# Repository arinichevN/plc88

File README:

Проект модульного контроллера plc88.
Инструментарий.
Электрические схемы и печатные платы разработаны с помощью KiCad. Библиотеки пользовательских компонентов для KiCad расположены в папке lib. Симуляция работы некоторых узлов производилась в программе https://falstad.com/circuit/circuitjs.html. Программное обеспечение для тестирования отдельных узлов написано на языке Си для Arduino IDE.
Предупреждение.
Представленные в этом проекте аппаратные и программные средства явлются прототипами и не оптимизированы для производства и профессионального использования. Они подходят для обучения но при использовании в реальных ситуациях, нет никакой гарантии, что они будут работать без аварий.

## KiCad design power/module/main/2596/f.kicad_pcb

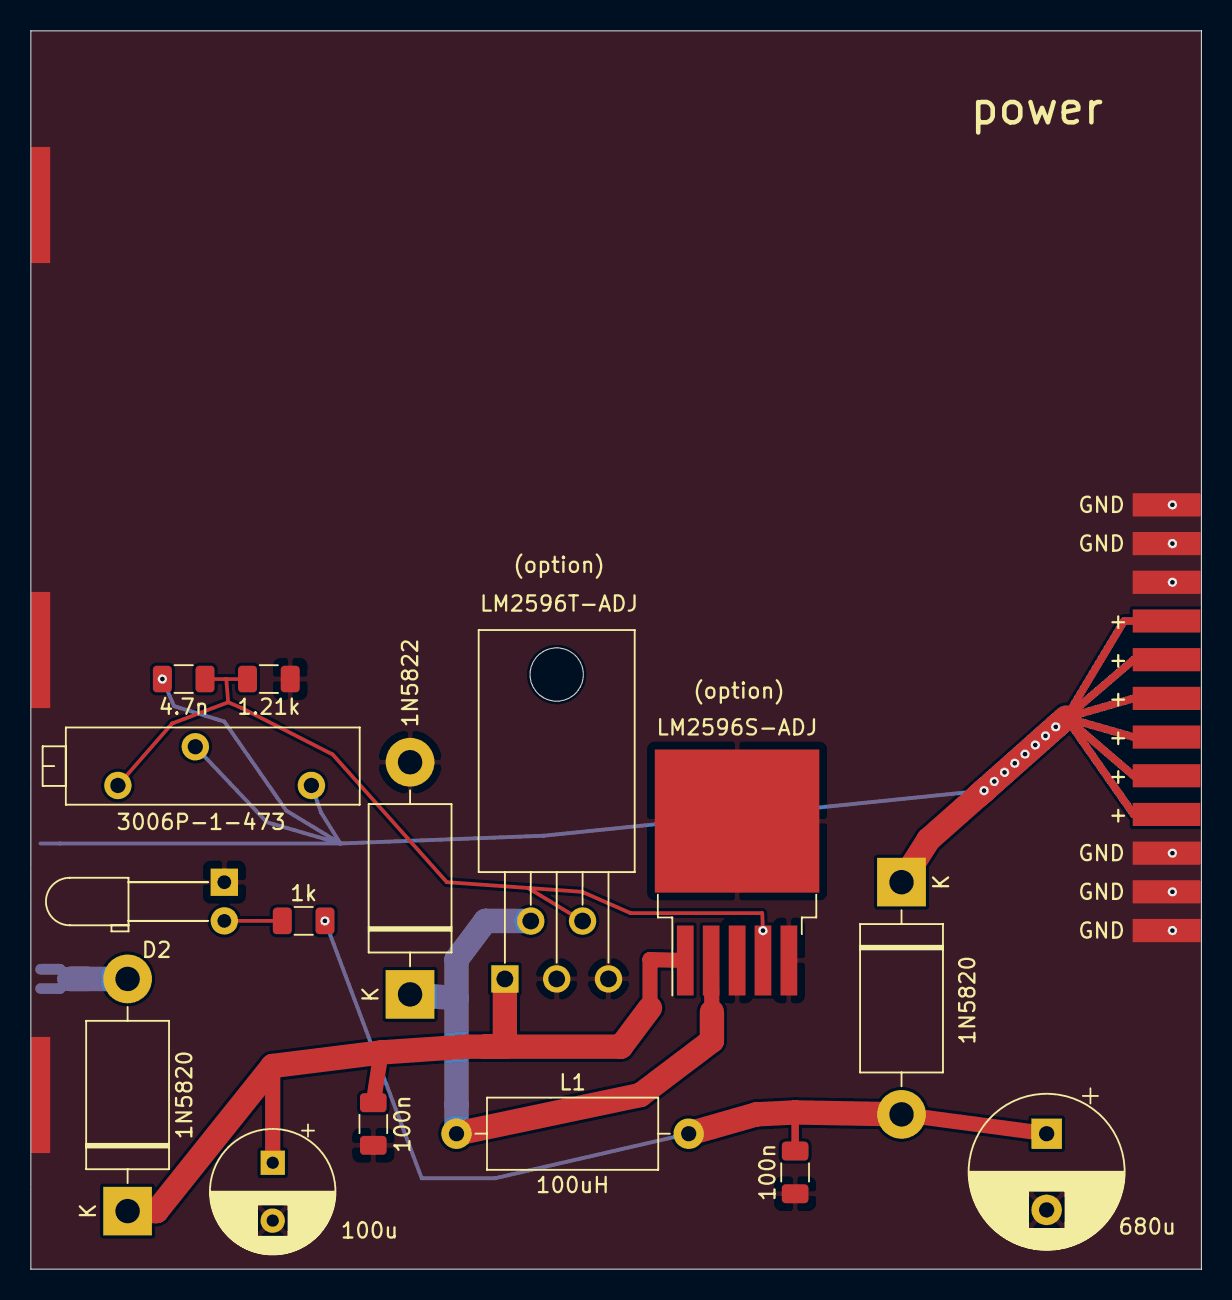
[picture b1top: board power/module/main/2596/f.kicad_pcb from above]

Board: 2 copper layers, 76.8 x 81.3 mm, 17 parts (0 on the bottom side), 8 nets.

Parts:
C1: 100u; CP_Radial_D8.0mm_P3.80mm
C2: 680u; CP_Radial_D10.0mm_P5.00mm
C3, C5: 100n; C_1206_3216Metric
C4: 4.7n; C_1206_3216Metric
D1, D4: 1N5820; D_DO-201AD_P15.24mm_Horizontal
D2: LED; LED_D3.0mm_Horizontal_O6.35mm_Z2.0mm
D3: 1N5822; D_DO-201AD_P15.24mm_Horizontal
J1: bus_power_i; bus_power_im
J2: fm_power_i; fm_power_im
L1: 100uH; L_Axial_L11.0mm_D4.5mm_P15.24mm_Horizontal_Fastron_MECC
R1: 1.21k; R_1206_3216Metric
R2: 1k; R_1206_3216Metric
RV1: 3006P-1-473; Potentiometer_Bourns_3006P_Horizontal
U1: LM2596S-ADJ; TO-263-5_TabPin3
U2: LM2596T-ADJ; TO-220-5_P3.4x3.8mm_StaggerOdd_Lead7.13mm_TabDown

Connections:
CFB: C4.2, R1.1, RV1.3, U1.4, U2.4
COUT: D3.1, L1.1, U1.2, U2.2
CVIN: C1.1, C3.1, D1.1, U1.1, U2.1
GND: C1.2, C2.2, C3.2, C5.2, D2.1, D3.2, J1.1, J1.2, J1.3, J1.4, J1.5, J1.6, J1.19, J1.20, J1.21, J1.22, J1.23, J1.24, J2.2, J2.4, J2.5, R1.2, U1.3, U1.5, U2.3, U2.5
unnamed: C2.1, C5.1, D4.2, L1.2, R2.1
unnamed: D2.2, R2.2
VIN: D1.2, J2.1
VOUT: C4.1, D4.1, J1.7, J1.8, J1.9, J1.10, J1.11, J1.12, J1.13, J1.14, J1.15, J1.16, J1.17, J1.18, J2.3, RV1.1, RV1.2

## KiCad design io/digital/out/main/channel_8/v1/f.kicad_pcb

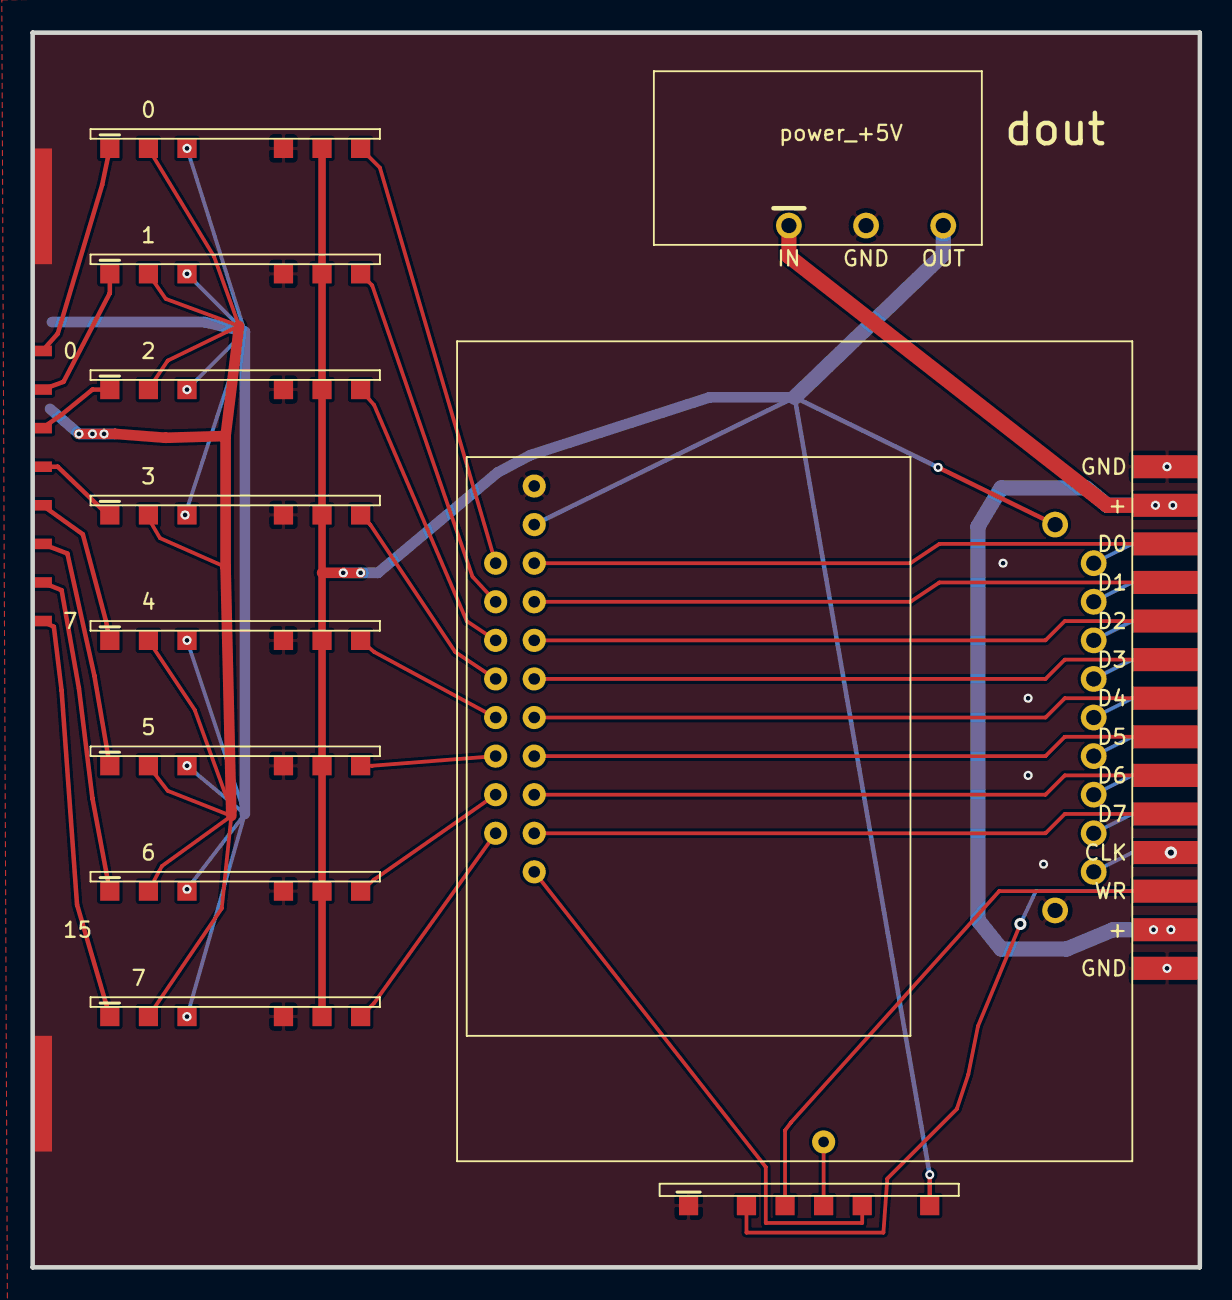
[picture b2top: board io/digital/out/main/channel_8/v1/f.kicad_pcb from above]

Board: 2 copper layers, 76.8 x 81.3 mm, 14 parts (0 on the bottom side), 42 nets.

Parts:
J1: fm16_i; fm16_im
J2, J3, J4, J5, J6, J7, J8, J9: dio_channel_i
J10: data_manager_i
J11: wrs_i
J12: selector4_i
J13: bus_i; bus_im
J14: power_+5V; power_i

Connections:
+5V: J2.5, J3.5, J4.5, J5.5, J6.5, J7.5, J8.5, J9.5, J10.18, J11.6, J12.1, J14.2
A0: J12.2, J13.5
A1: J12.3, J13.7
A2: J12.4, J13.9
A3: J12.5, J13.11
A4: J12.6, J13.13
A5: J12.7, J13.15
A6: J12.8, J13.17
A7: J12.9, J13.19
CLK: J12.10, J13.21, J13.22
D0: J10.2, J13.6
D1: J10.4, J13.8
D2: J10.6, J13.10
D3: J10.8, J13.12
D4: J10.10, J13.14
D5: J10.12, J13.16
D6: J10.14, J13.18
D7: J10.16, J13.20
GND: J1.21, J1.22, J1.23, J1.24, J1.25, J2.4, J3.4, J4.4, J5.4, J6.4, J7.4, J8.4, J9.4, J10.17, J11.1, J12.11, J13.1, J13.2, J13.27, J13.28, J14.3
OPL0: J2.6, J10.1
OPL1: J3.6, J10.3
OPL2: J4.6, J10.5
OPL3: J5.6, J10.7
OPL4: J6.6, J10.9
OPL5: J7.6, J10.11
OPL6: J8.6, J10.13
OPL7: J9.6, J10.15
OUT0: J1.1, J2.1
OUT1: J1.2, J3.1
OUT2: J1.3, J4.1
OUT3: J1.4, J5.1
OUT4: J1.5, J6.1
OUT5: J1.6, J7.1
OUT6: J1.7, J8.1
OUT7: J1.8, J9.1
RD: J11.2, J13.23
S0: J11.4, J12.12
SW0: J10.19, J11.5
VM0_7: J1.17, J2.3, J3.3, J4.3, J5.3, J6.3, J7.3, J8.3, J9.3
VP0_7: J1.18, J2.2, J3.2, J4.2, J5.2, J6.2, J7.2, J8.2, J9.2
VPBUS: J13.3, J13.4, J13.25, J13.26, J14.1
WR: J11.3, J13.24

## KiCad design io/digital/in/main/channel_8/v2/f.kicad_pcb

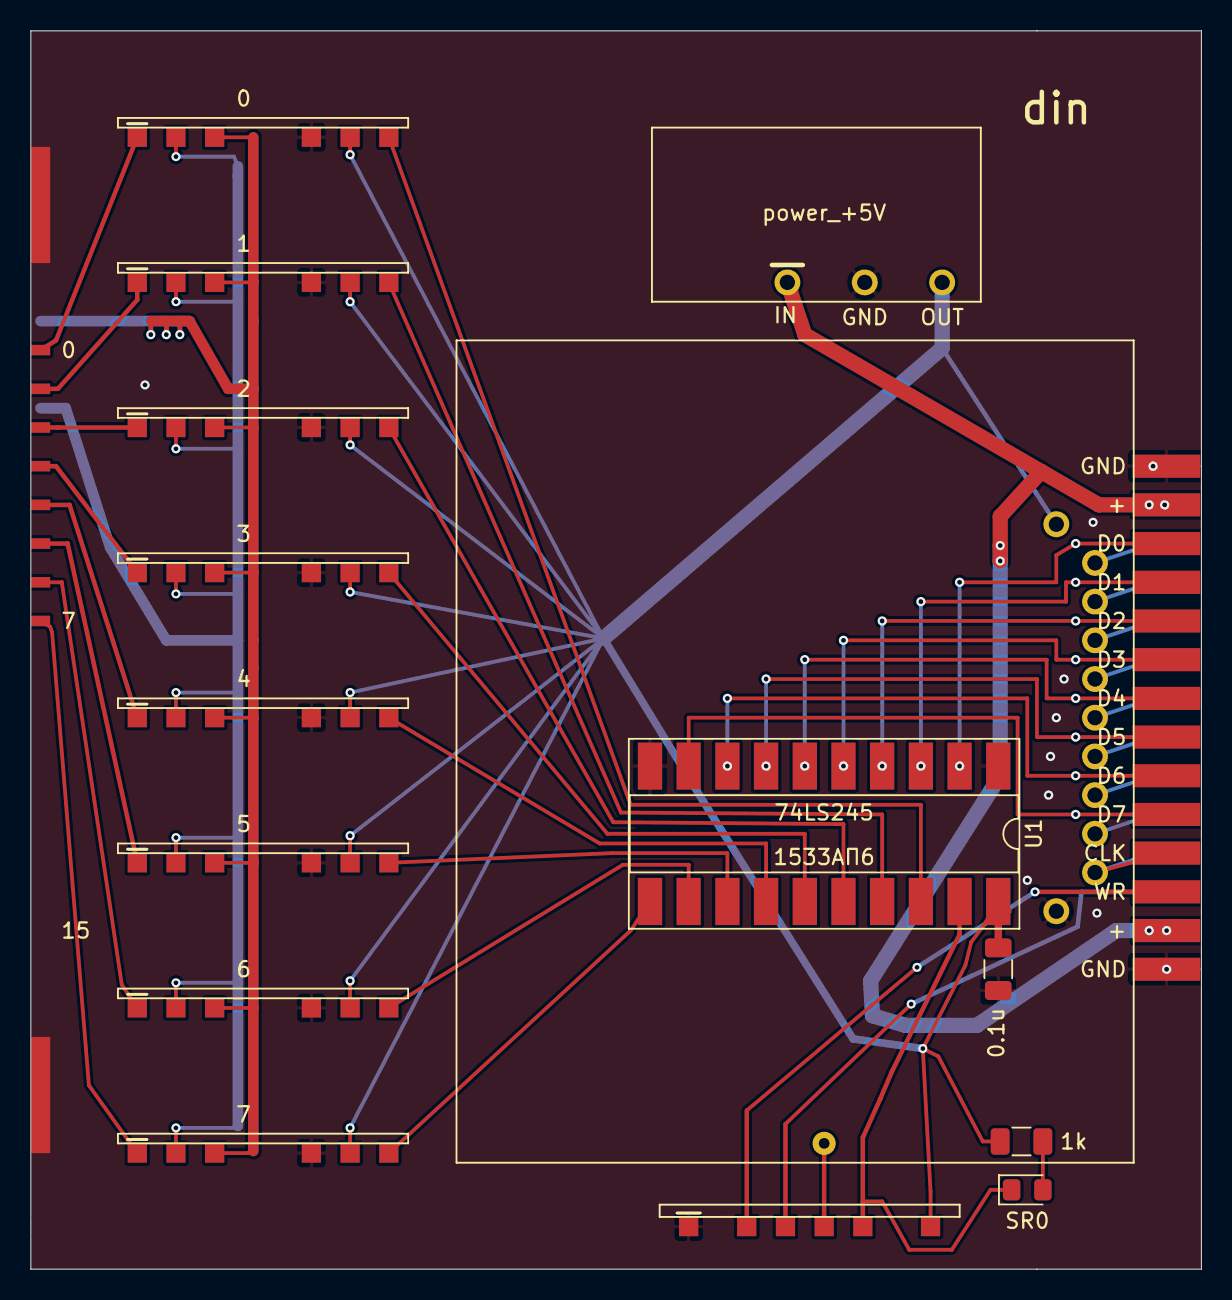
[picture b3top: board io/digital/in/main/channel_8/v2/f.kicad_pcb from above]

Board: 2 copper layers, 76.8 x 81.3 mm, 17 parts (0 on the bottom side), 43 nets.

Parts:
C1: 0.1u; C_1206_3216Metric
D1: SR0; LED_0805_2012Metric_Pad1.15x1.40mm_HandSolder
J1: fm16_i; fm16_im
J2, J3, J4, J5, J6, J7, J8, J9: dio_channel_i
J10: wrs_i
J11: selector4_i
J12: power_+5V; power_i
J13: bus_i; bus_im
R1: 1k; R_1206_3216Metric
U1: 74LS245; DIP-20_W8.89mm_SMDSocket_LongPads

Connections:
+5V: C1.2, J2.5, J3.5, J4.5, J5.5, J6.5, J7.5, J8.5, J9.5, J10.6, J11.1, J12.2, R1.1, U1.20
A0: J11.2, J13.5
A1: J11.3, J13.7
A2: J11.4, J13.9
A3: J11.5, J13.11
A4: J11.6, J13.13
A5: J11.7, J13.15
A6: J11.8, J13.17
A7: J11.9, J13.19
CLK: J11.10, J13.21, J13.22
D0: J13.6, U1.2
D1: J13.8, U1.3
D2: J13.10, U1.4
D3: J13.12, U1.5
D4: J13.14, U1.6
D5: J13.16, U1.7
D6: J13.18, U1.8
D7: J13.20, U1.9
GND: C1.1, J1.21, J1.22, J1.23, J1.24, J1.25, J2.4, J3.4, J4.4, J5.4, J6.4, J7.4, J8.4, J9.4, J10.1, J11.11, J12.3, J13.1, J13.2, J13.27, J13.28, U1.1, U1.10
GND0_7: J1.17, J2.3, J3.3, J4.3, J5.3, J6.3, J7.3, J8.3, J9.3
IN0: J1.1, J2.1
IN1: J1.2, J3.1
IN2: J1.3, J4.1
IN3: J1.4, J5.1
IN4: J1.5, J6.1
IN5: J1.6, J7.1
IN6: J1.7, J8.1
IN7: J1.8, J9.1
INL0: J2.6, U1.18
INL1: J3.6, U1.17
INL2: J4.6, U1.16
INL3: J5.6, U1.15
INL4: J6.6, U1.14
INL5: J7.6, U1.13
INL6: J8.6, U1.12
INL7: J9.6, U1.11
unnamed: D1.2, R1.2
RD: J10.3, J13.23
S0: J10.4, J11.12
SR0: D1.1, J10.5, U1.19
V0_7: J1.18, J2.2, J3.2, J4.2, J5.2, J6.2, J7.2, J8.2, J9.2
VPBUS: J12.1, J13.3, J13.4, J13.25, J13.26
WR: J10.2, J13.24

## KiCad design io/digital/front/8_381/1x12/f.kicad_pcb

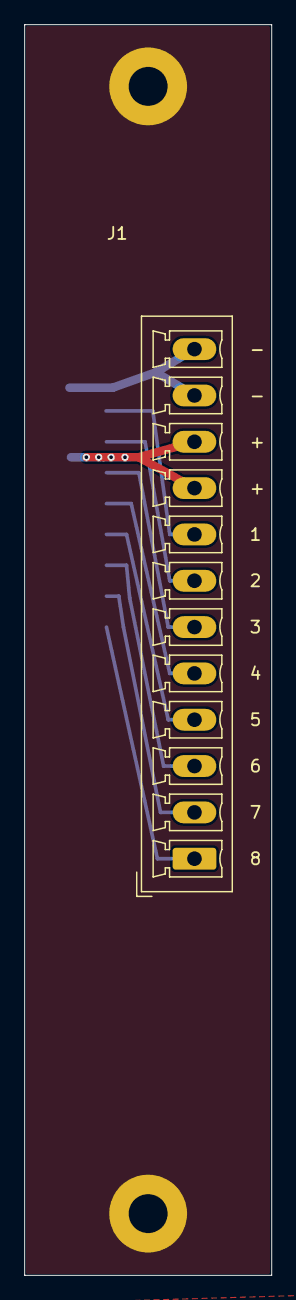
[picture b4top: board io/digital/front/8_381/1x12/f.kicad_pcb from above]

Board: 2 copper layers, 20.3 x 102.9 mm, 4 parts (0 on the bottom side), 11 nets.

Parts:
H1, H2: MountingHole_Pad; MountingHole_3.2mm_M3_Pad
J1: fm16_i
J2: Conn_01x12; PhoenixContact_MCV_1,5_12-G-3.81_1x12_P3.81mm_Vertical

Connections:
GND: H1.1, H2.1, J1.21, J1.22, J1.23, J1.24, J1.25
L0: J1.1, J2.8
L1: J1.2, J2.7
L2: J1.3, J2.6
L3: J1.4, J2.5
L4: J1.5, J2.4
L5: J1.6, J2.3
L6: J1.7, J2.2
L7: J1.8, J2.1
VM0_7: J1.17, J2.11, J2.12
VP0_7: J1.18, J2.9, J2.10

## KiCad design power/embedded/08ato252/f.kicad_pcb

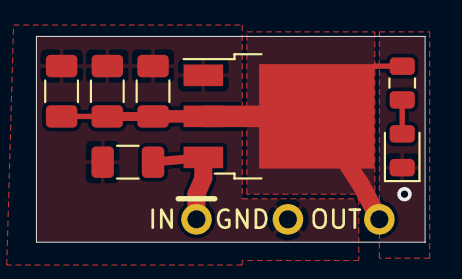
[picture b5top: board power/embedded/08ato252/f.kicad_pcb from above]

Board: 2 copper layers, 21.6 x 11.4 mm, 8 parts (0 on the bottom side), 4 nets.

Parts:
C1: 1u; C_1206_3216Metric
C2, C3, C4: 10u; C_1206_3216Metric
D1: LED; LED_0805_2012Metric
J1: power_i; power_im
R1: 1k; R_0805_2012Metric
U1: LM1117-5.0; TO-252-3_TabPin2

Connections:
GND: C1.2, C2.2, C3.2, C4.2, D1.1, J1.3, U1.1
unnamed: D1.2, R1.1
VIN: C1.1, J1.1, U1.3
VOUT: C2.1, C3.1, C4.1, J1.2, R1.2, U1.2

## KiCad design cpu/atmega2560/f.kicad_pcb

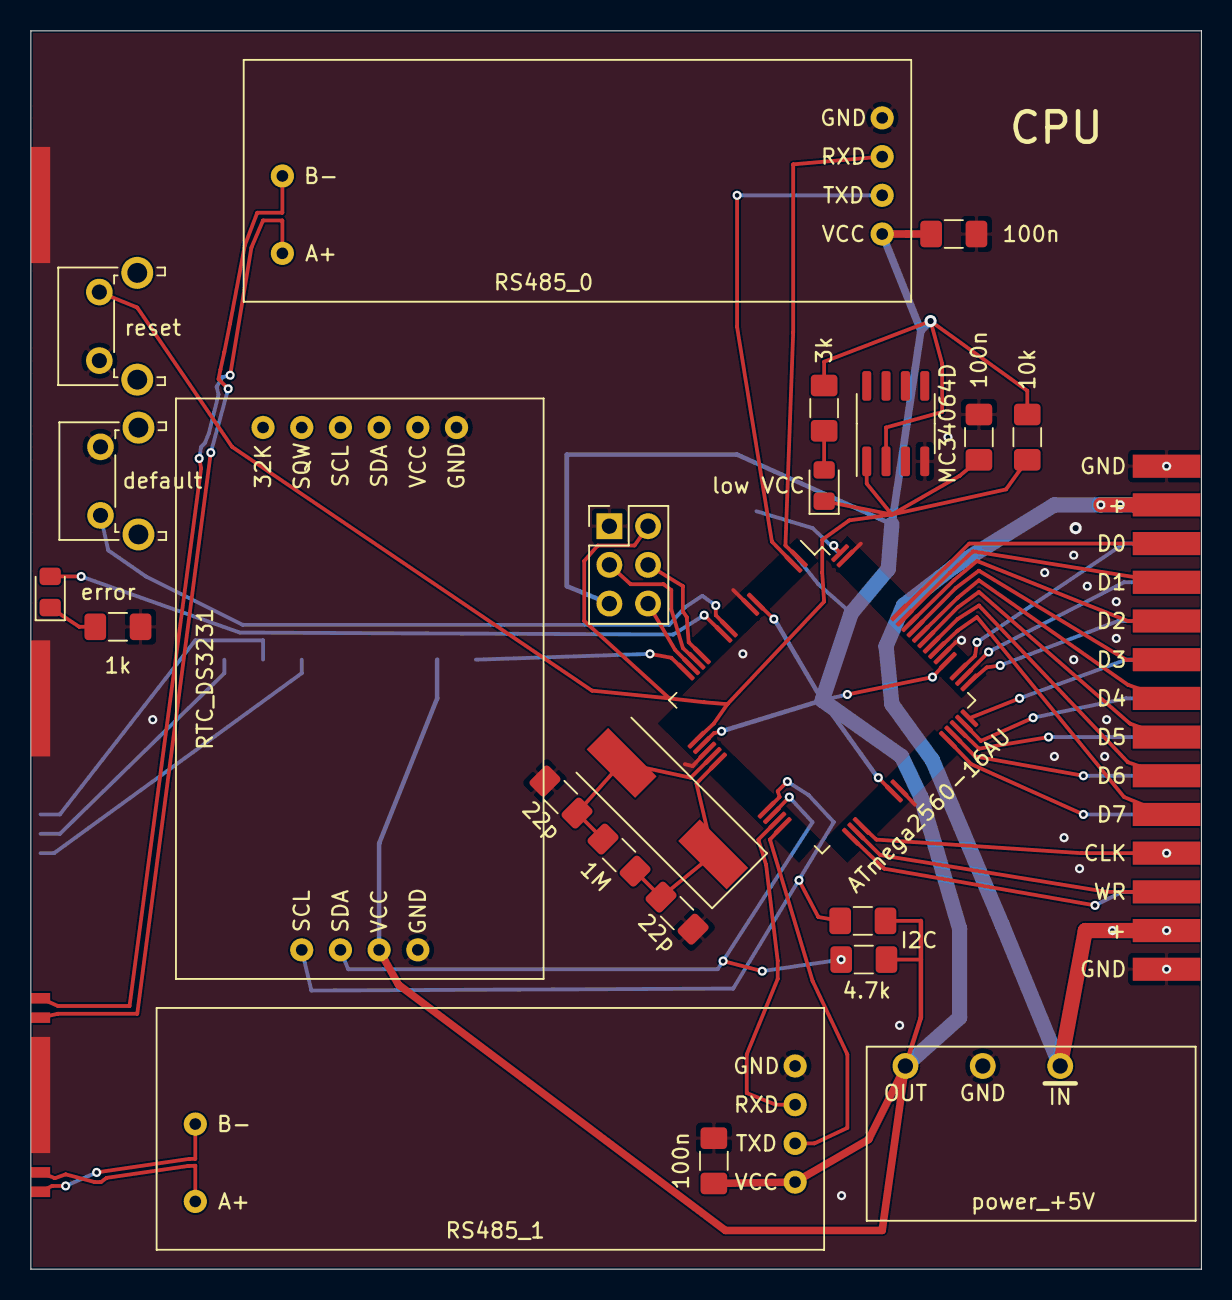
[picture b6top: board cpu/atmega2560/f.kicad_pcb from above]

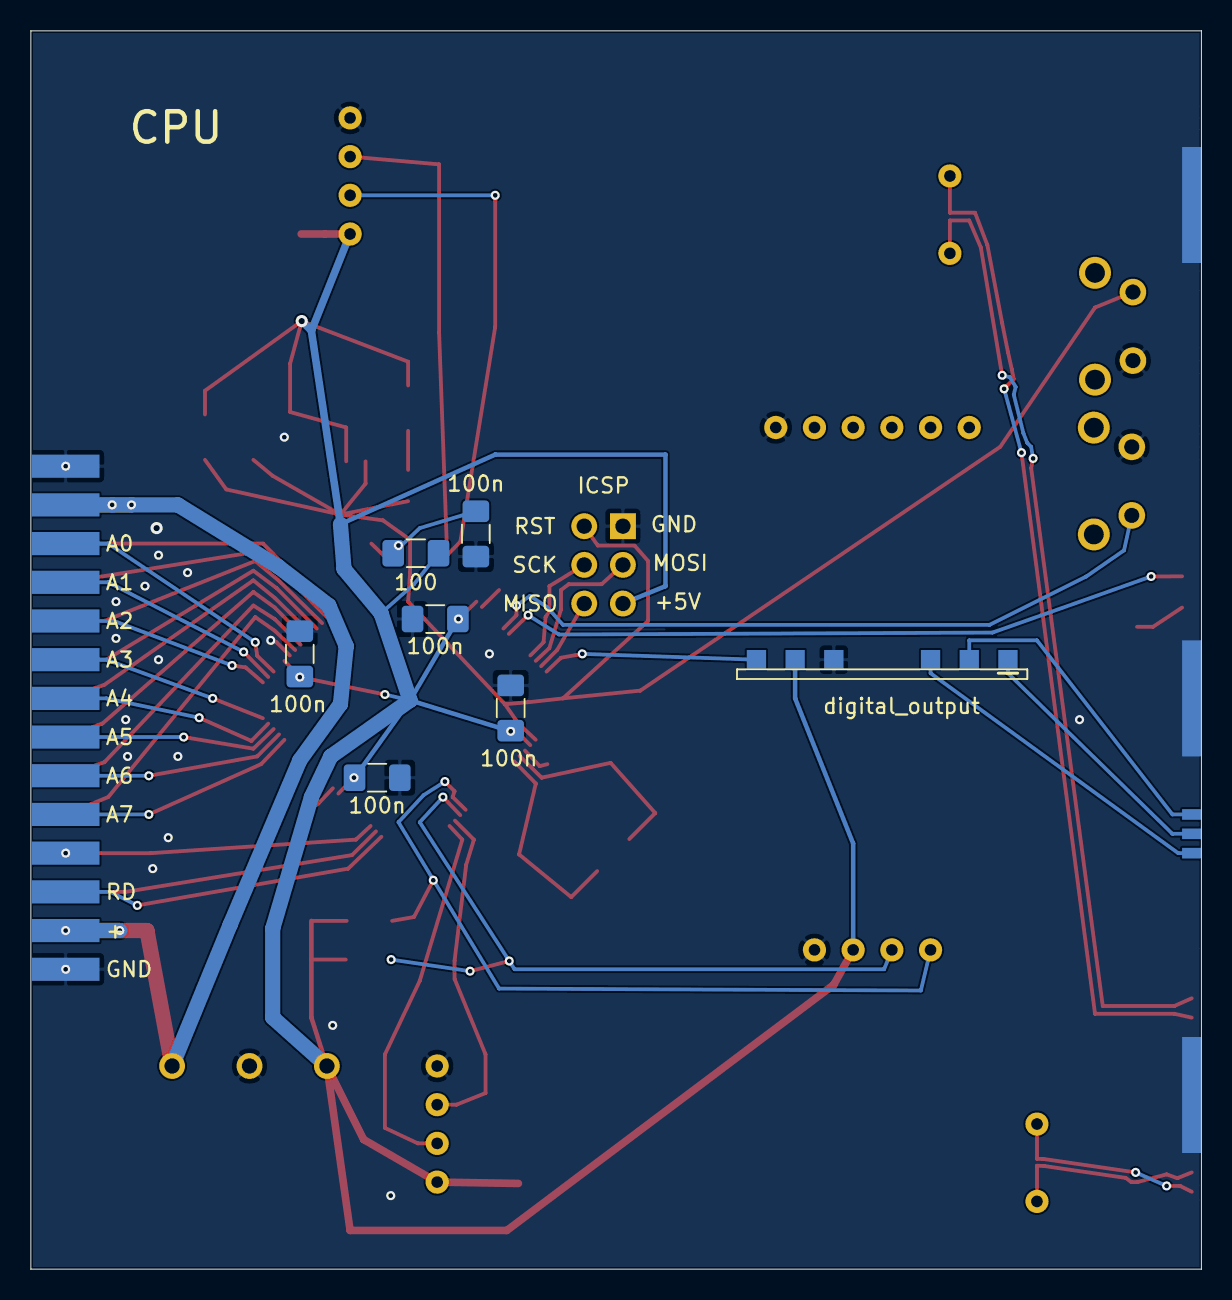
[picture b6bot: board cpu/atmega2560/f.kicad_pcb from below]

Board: 2 copper layers, 76.8 x 81.3 mm, 32 parts (7 on the bottom side), 47 nets.

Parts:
C1, C2, C3, C4, C7, C8, C9, C10: 100n; C_1206_3216Metric_Pad1.42x1.75mm_HandSolder
C5, C6: 22p; C_1206_3216Metric_Pad1.42x1.75mm_HandSolder
D1: error; LED_0805_2012Metric_Pad1.15x1.40mm_HandSolder
D2: low VCC; LED_0805_2012Metric_Pad1.15x1.40mm_HandSolder
J1: bus; bus_im
J2: ICSP; PinHeader_2x03_P2.54mm_Vertical
J3: fm_cpu_i; fm_cpu_im
J4: digital_output; dio_channel_i
J5: power_+5V; power_i
J10: RS485_0; rs485_i
J11: RS485_1; rs485_i
J14: RTC_DS3231; rtc_ds3231_i
R1: 1M; R_1206_3216Metric_Pad1.42x1.75mm_HandSolder
R2: 1k; R_1206_3216Metric_Pad1.42x1.75mm_HandSolder
R3: 3k; R_1206_3216Metric_Pad1.42x1.75mm_HandSolder
R4: 10k; R_1206_3216Metric_Pad1.42x1.75mm_HandSolder
R5: 100; R_1206_3216Metric_Pad1.42x1.75mm_HandSolder
R6, R7: 4.7k; R_1206_3216Metric_Pad1.42x1.75mm_HandSolder
SW1: default; SW_Tactile_SPST_Angled_PTS645Vx83-2LFS
SW2: reset; SW_Tactile_SPST_Angled_PTS645Vx83-2LFS
U1: ATmega2560-16AU; TQFP-100_14x14mm_P0.5mm
U4: MC34064D; SOIC-8_3.9x4.9mm_P1.27mm
Y1: 16M; Crystal_SMD_HC49-SD

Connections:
+5V: C1.1, C2.1, C3.1, C4.1, C7.1, C8.1, J2.5, J4.5, J5.2, J10.1, J11.1, J14.3, R3.1, R4.1, R5.2, R6.2, R7.2, U1.10, U1.31, U1.61, U1.80, U4.2
A0: J1.5, U1.78
A0+: J3.4, J10.5
A1: J1.7, U1.77
A1+: J3.6, J11.5
A2: J1.9, U1.76
A3: J1.11, U1.75
A4: J1.13, U1.74
A5: J1.15, U1.73
A6: J1.17, U1.72
A7: J1.19, U1.71
AVCC: C10.2, R5.1, U1.100
B0-: J3.5, J10.6
B1-: J3.7, J11.6
CLK: J1.21, J1.22, U1.55
D0: J1.6, U1.89
D1: J1.8, U1.88
D2: J1.10, U1.87
D3: J1.12, U1.86
D4: J1.14, U1.85
D5: J1.16, U1.84
D6: J1.18, U1.83
D7: J1.20, U1.82
DEFAULT: SW1.1, U1.15
ERROR: D1.2, U1.16
GND: C1.2, C2.2, C3.2, C4.2, C5.2, C6.2, C7.2, C8.2, C9.1, C10.1, J1.1, J1.2, J1.27, J1.28, J2.1, J3.8, J4.4, J5.3, J10.4, J11.4, J14.4, J14.10, R2.1, SW1.2, SW2.1, U1.11, U1.32, U1.62, U1.81, U1.99, U4.4
MISO: J2.6, U1.22
MOSI: J2.3, U1.21
unnamed: D1.1, R2.2
unnamed: D2.2, R3.2
RD: J1.23, U1.53
READY: J4.6, U1.23
READY_O: J3.2, J4.1
RST: C9.2, D2.1, J2.2, R4.2, SW2.2, U1.30, U4.1
RX0: J10.3, U1.2
RX1: J11.3, U1.45
SCK: J2.4, U1.20
SCL: J14.1, R6.1, U1.43
SDA: J14.2, R7.1, U1.44
TX0: J10.2, U1.3
TX1: J11.2, U1.46
VMOUT: J3.3, J4.3
VP: J1.3, J1.4, J1.25, J1.26, J5.1
VPOUT: J3.1, J4.2
WR: J1.24, U1.54
XTAL1: C5.1, R1.1, U1.34, Y1.1
XTAL2: C6.1, R1.2, U1.33, Y1.2

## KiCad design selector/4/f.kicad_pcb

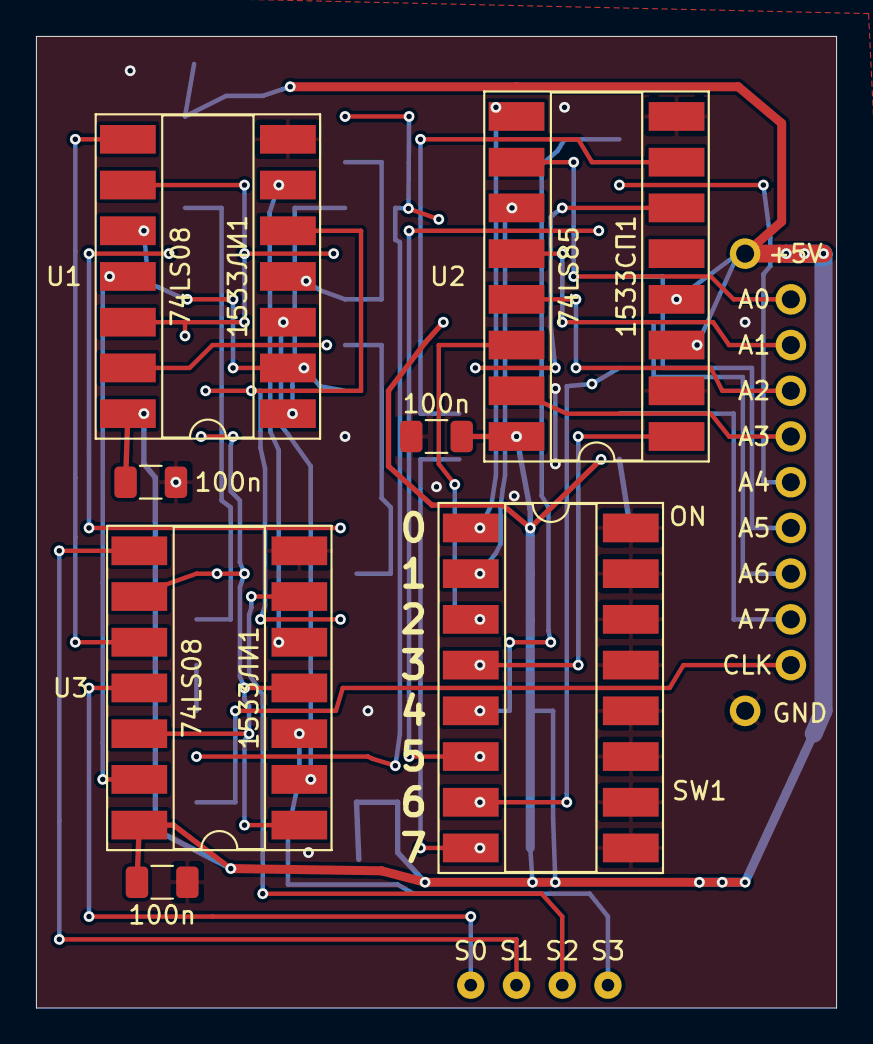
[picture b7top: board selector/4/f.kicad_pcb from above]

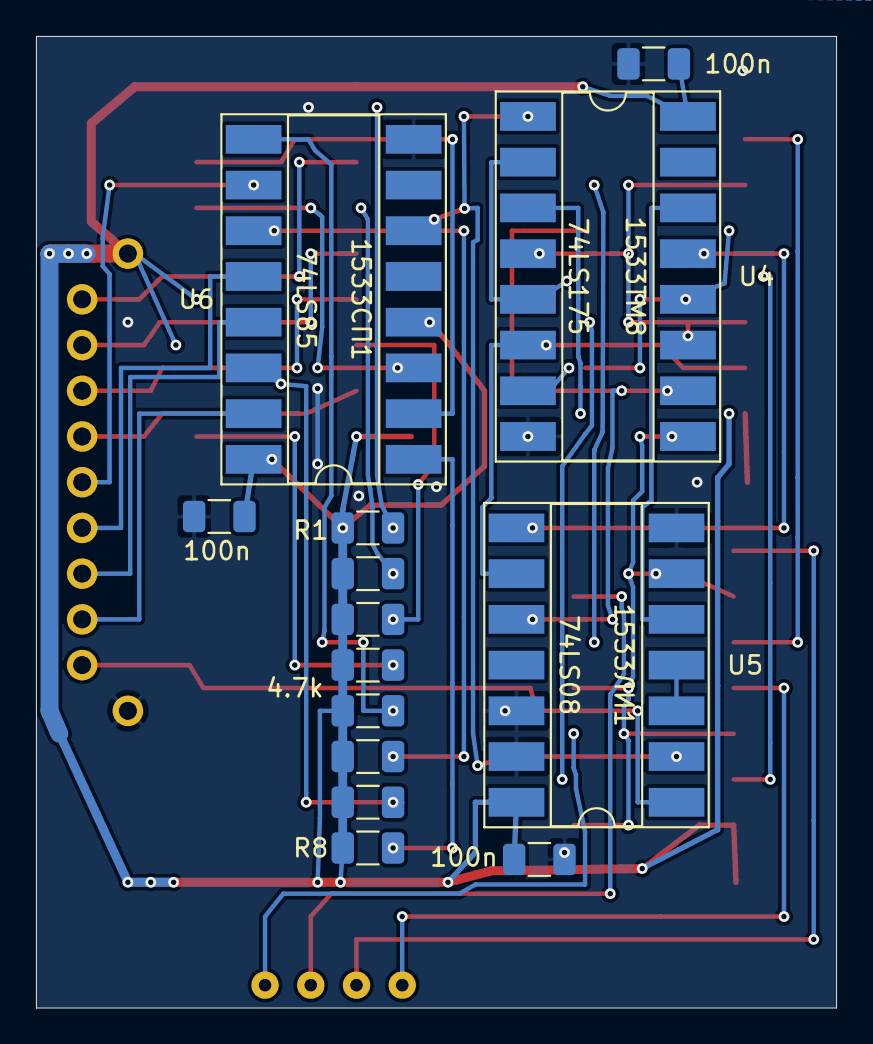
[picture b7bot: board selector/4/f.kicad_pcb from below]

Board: 2 copper layers, 44.5 x 54.0 mm, 22 parts (14 on the bottom side), 40 nets.

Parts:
C1, C2, C3, C4, C5, C6: 100n; C_1206_3216Metric
J1: selector4_i; selector4_im
R1, R2, R3, R4, R5, R6, R7, R8: 4.7k; R_1206_3216Metric
SW1: SW_DIP_x08; DIP-16_W8.89mm_SMDSocket_LongPads
U1, U3, U5: 74LS08; DIP-14_W8.89mm_SMDSocket_LongPads
U2, U6: 74LS85; DIP-16_W8.89mm_SMDSocket_LongPads
U4: 74LS175; DIP-16_W8.89mm_SMDSocket_LongPads

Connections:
+5V: C1.1, C2.1, C3.1, C4.1, C5.1, C6.1, J1.1, R1.1, R2.1, R3.1, R4.1, R5.1, R6.1, R7.1, R8.1, U1.14, U2.3, U2.4, U2.16, U3.14, U4.16, U5.14, U6.4, U6.16
A0: J1.2, U2.10
A1: J1.3, U2.12
A2: J1.4, U2.13
A3: J1.5, U2.15
A4: J1.6, U6.10
A5: J1.7, U6.12
A6: J1.8, U6.13
A7: J1.9, U6.15
ADDR_OK: U4.1, U5.2, U6.6
B0: R1.2, SW1.1, U2.9
B1: R2.2, SW1.2, U2.11
B2: R3.2, SW1.3, U2.14
B3: R4.2, SW1.4, U2.1
B4: R5.2, SW1.5, U6.9
B5: R6.2, SW1.6, U6.11
B6: R7.2, SW1.7, U6.14
B7: R8.2, SW1.8, U6.1
CLK: J1.10, U5.1
CLK_AFB: U3.1, U3.4, U3.9, U3.12, U4.9, U5.6
FB: U4.14, U5.5
GND: C1.2, C2.2, C3.2, C4.2, C5.2, C6.2, J1.11, SW1.9, SW1.10, SW1.11, SW1.12, SW1.13, SW1.14, SW1.15, SW1.16, U1.7, U2.2, U2.8, U3.7, U4.8, U5.7, U5.12, U5.13, U6.8
unnamed: U1.3, U3.2
unnamed: U1.6, U3.5
unnamed: U1.8, U3.10
unnamed: U1.11, U3.13
unnamed: U2.6, U6.3
unnamed: U2.7, U6.2
unnamed: U4.13, U5.8
unnamed: U5.3, U5.4
P1: U1.9, U1.12, U4.4, U4.11
P2: U1.1, U4.3
P3: U1.4, U4.2, U4.5
P4: U1.13, U4.6, U5.9
P5: U1.2, U1.10, U4.7, U4.12
P6: U1.5, U4.10, U5.10
S0: J1.12, U3.11
S1: J1.13, U3.8
S2: J1.14, U3.6
S3: J1.15, U3.3

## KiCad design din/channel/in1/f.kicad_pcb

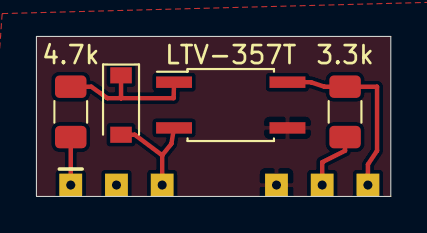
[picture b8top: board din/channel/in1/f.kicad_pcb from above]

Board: 2 copper layers, 19.7 x 8.9 mm, 5 parts (0 on the bottom side), 6 nets.

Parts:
D1: 1N4148W; D_SOD-123
J1: dio_channel_i; dio_channel_im
R1: 4.7k; R_1206_3216Metric
R2: 3.3k; R_1206_3216Metric
U1: LTV-357T; SO-4_4.4x3.6mm_P2.54mm

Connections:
+5V: J1.5, R2.1
GND: J1.4, U1.3
IN: J1.1, R1.2
unnamed: D1.1, R1.1, U1.1
OUT: J1.6, R2.2, U1.4
VINM: D1.2, J1.3, U1.2

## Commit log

2023-04-07 voltage regulator for each module
2023-04-08 + 2596 power supply module
